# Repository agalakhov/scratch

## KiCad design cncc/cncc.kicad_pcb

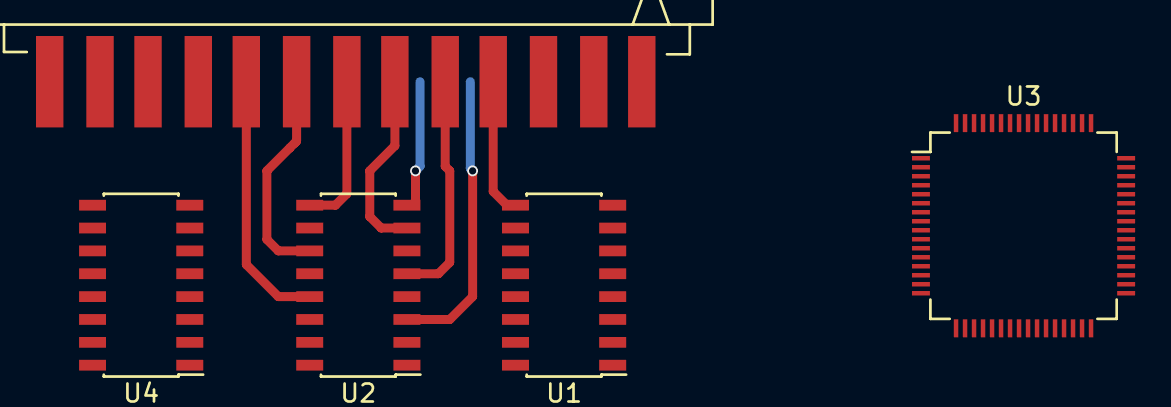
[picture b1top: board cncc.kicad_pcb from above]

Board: 2 copper layers, 5 parts (0 on the bottom side), 19 nets.

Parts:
J1: DB25; DB25M_CI
U1, U2: 74HCT365; SOIC-16_3.9x9.9mm_Pitch1.27mm
U3: STM32F405R; LQFP-64_10x10mm_Pitch0.5mm
U4: 4050; SOIC-16_3.9x9.9mm_Pitch1.27mm

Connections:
GND: J1.18, J1.19, J1.20, J1.21, J1.22, J1.23, J1.24, J1.25, U1.8, U2.8
unnamed: J1.1, U1.3
unnamed: J1.2, U1.7
unnamed: J1.3, U1.13
unnamed: J1.4, U1.9
unnamed: J1.5, U2.5
unnamed: J1.6, U2.7
unnamed: J1.7, U2.9
unnamed: J1.8, U2.11
unnamed: J1.9, U2.13
unnamed: J1.10, U4.3
unnamed: J1.11, U4.7
unnamed: J1.12, U4.5
unnamed: J1.13, U4.9
unnamed: J1.14, U1.5
unnamed: J1.15, U4.11
unnamed: J1.16, U1.11
unnamed: J1.17, U2.3
VCC: U1.16, U2.16, U4.1

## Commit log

2015-11-19 perspective matrix
2015-11-22 phong `
2015-11-22 readme
2015-11-22 rtcheck
2015-11-22 primes/factor
2015-11-22 nominal
2016-04-08 cortex-m4 test
2016-06-14 cncc
